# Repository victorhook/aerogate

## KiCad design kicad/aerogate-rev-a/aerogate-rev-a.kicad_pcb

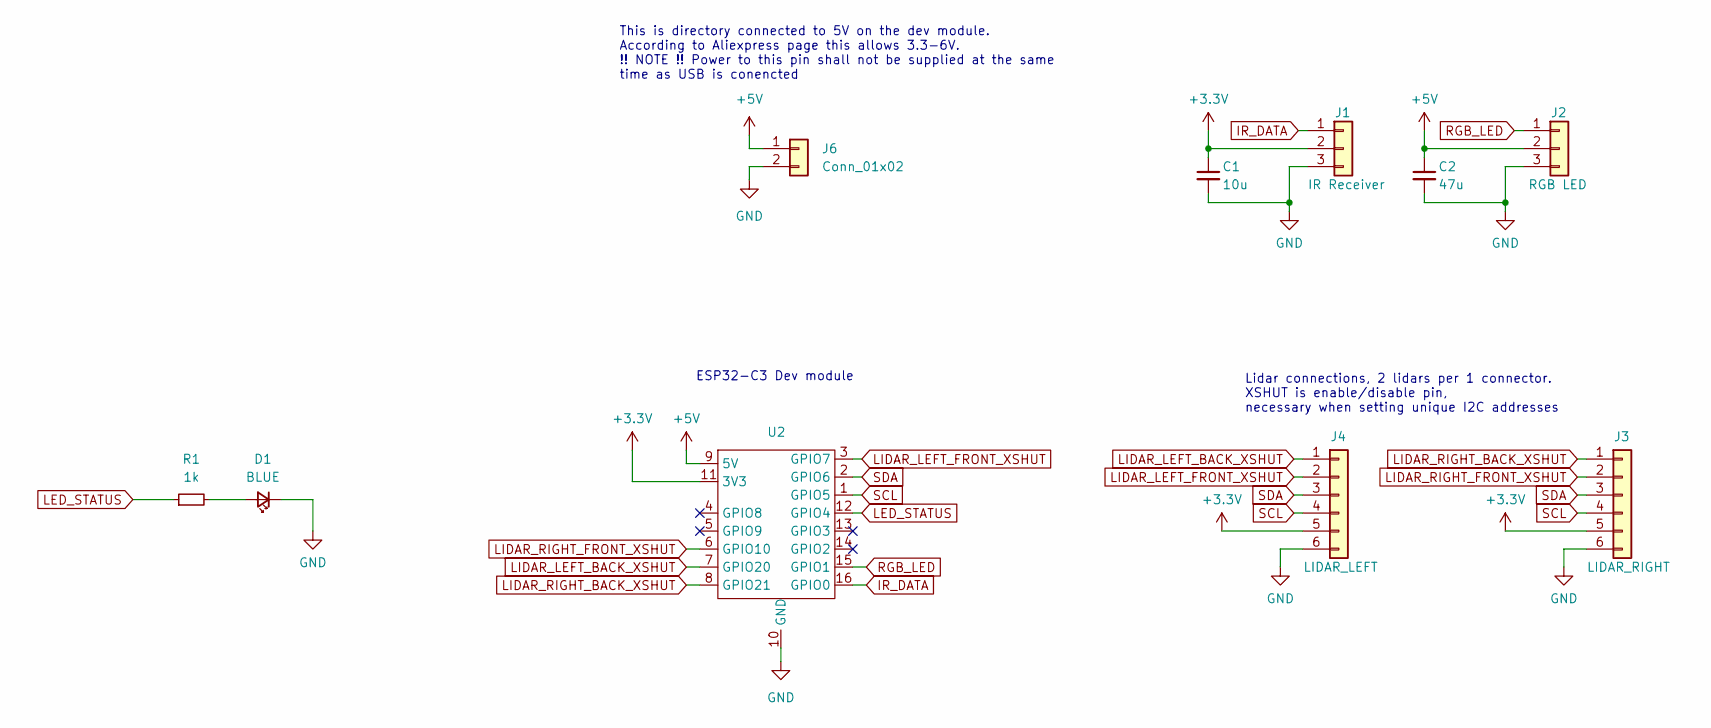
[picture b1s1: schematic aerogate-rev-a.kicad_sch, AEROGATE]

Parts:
C1: 10u; C_0603_1608Metric
C2: 47u; C_1206_3216Metric
D1: BLUE; LED_0603_1608Metric
J1: IR Receiver; PinSocket_1x03_P2.54mm_Vertical
J2: RGB LED; PinSocket_1x03_P2.54mm_Vertical
J3: LIDAR_RIGHT; PinSocket_1x06_P2.54mm_Vertical
J4: LIDAR_LEFT; PinSocket_1x06_P2.54mm_Vertical
J6: Conn_01x02; PinSocket_1x02_P2.54mm_Vertical
R1: 1k; R_0402_1005Metric
U2: ESP32-C3-Dev_Module

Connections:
+3.3V: C1.1, J1.2, J3.5, J4.5, U2.11 (3V3)
+5V: C2.1, J2.2, J6.1, U2.9 (5V)
GND: C1.2, C2.2, D1.1 (K), J1.3, J2.3, J3.6, J4.6, J6.2, U2.10 (GND)
IR_DATA: J1.1, U2.16 (GPIO0)
LED_STATUS: R1.1, U2.12 (GPIO4)
LIDAR_LEFT_BACK_XSHUT: J4.1, U2.7 (GPIO20)
LIDAR_LEFT_FRONT_XSHUT: J4.2, U2.3 (GPIO7)
LIDAR_RIGHT_BACK_XSHUT: J3.1, U2.8 (GPIO21)
LIDAR_RIGHT_FRONT_XSHUT: J3.2, U2.6 (GPIO10)
unnamed: D1.2 (A), R1.2
RGB_LED: J2.1, U2.15 (GPIO1)
SCL: J3.4, J4.4, U2.1 (GPIO5)
SDA: J3.3, J4.3, U2.2 (GPIO6)

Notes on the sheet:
ESP32-C3 Dev module
This is directory connected to 5V on the dev module. According to Aliexpress page this allows 3.3-6V. !! NOTE !! Power to this pin shall not be supplied at the same time as USB is conencted
Lidar connections, 2 lidars per 1 connector. XSHUT is enable/disable pin, necessary when setting unique I2C addresses

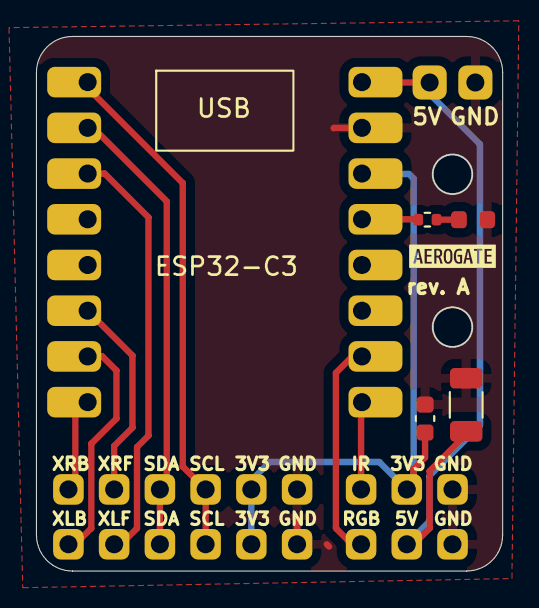
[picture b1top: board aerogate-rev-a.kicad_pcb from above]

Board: 2 copper layers, 25.8 x 29.7 mm, 11 parts (0 on the bottom side), 13 nets.

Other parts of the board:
kibuzzard-65C12A54: G***; kibuzzard-65C12A54

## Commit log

2024-02-05 Carrier PCB rev. A done
